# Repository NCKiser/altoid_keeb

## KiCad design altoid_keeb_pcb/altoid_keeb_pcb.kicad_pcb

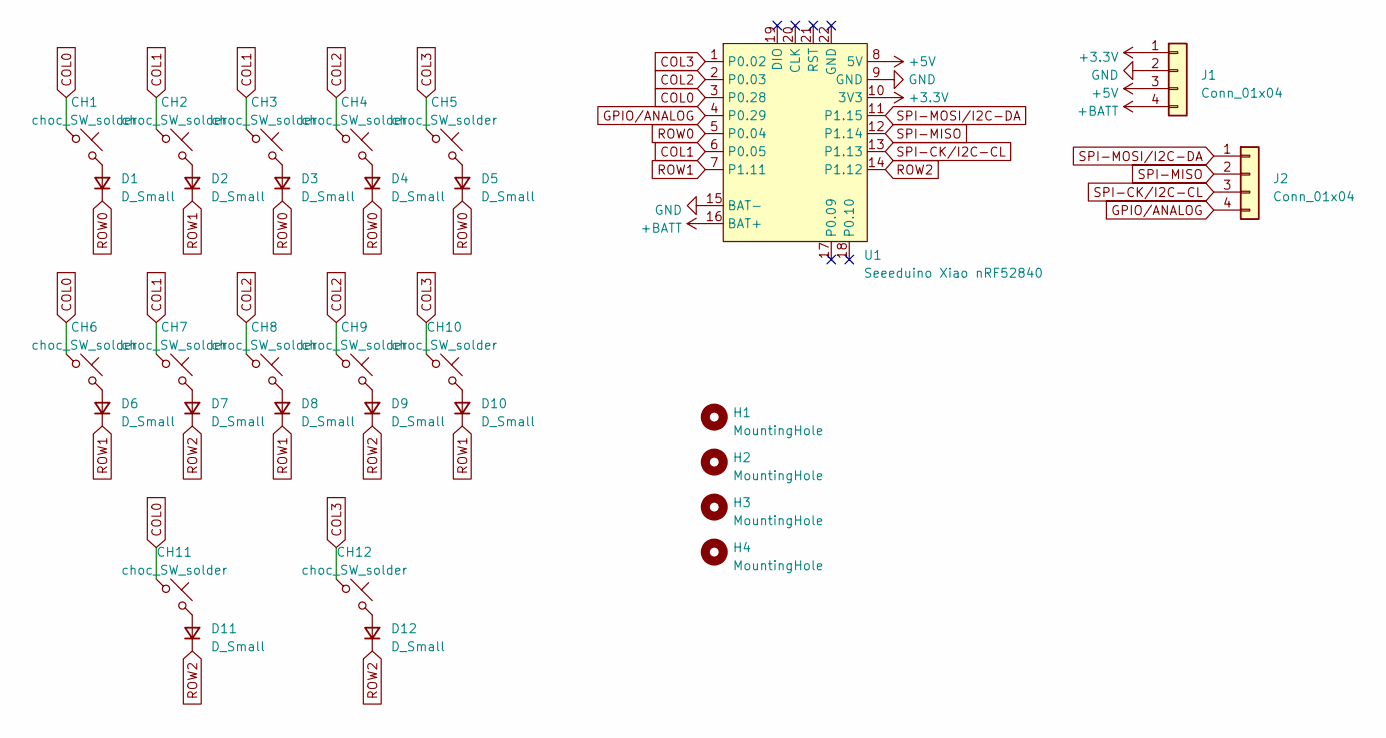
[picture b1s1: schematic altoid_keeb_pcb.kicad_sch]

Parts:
CH1, CH2, CH3, CH4, CH5, CH6, CH7, CH8, CH9, CH10, CH11, CH12: choc_SW_solder; SW_choc_v1+v2_1u
D1, D2, D3, D4, D5, D6, D7, D8, D9, D10, D11, D12: D_Small; D_DO-34_SOD68_P7.62mm_Horizontal
H1, H2, H3, H4: MountingHole; MountingHole_2.2mm_M2_Pad_Via
J1, J2: Conn_01x04; PinHeader_1x04_P2.54mm_Vertical
U1: Seeeduino Xiao nRF52840; Xiao_nRF52840_ACH

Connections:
+3.3V: J1.1, U1.10 (3V3)
+5V: J1.3, U1.8 (5V)
+BATT: J1.4, U1.16 (BAT+)
COL0: CH1.1, CH6.1, CH11.1, U1.3 (P0.28)
COL1: CH2.1, CH3.1, CH7.1, U1.6 (P0.05)
COL2: CH4.1, CH8.1, CH9.1, U1.2 (P0.03)
COL3: CH5.1, CH10.1, CH12.1, U1.1 (P0.02)
GND: J1.2, U1.9 (GND), U1.15 (BAT-)
GPIO/ANALOG: J2.4, U1.4 (P0.29)
unnamed: CH1.2, D1.2 (A)
unnamed: CH2.2, D2.2 (A)
unnamed: CH3.2, D3.2 (A)
unnamed: CH4.2, D4.2 (A)
unnamed: CH5.2, D5.2 (A)
unnamed: CH6.2, D6.2 (A)
unnamed: CH7.2, D7.2 (A)
unnamed: CH8.2, D8.2 (A)
unnamed: CH9.2, D9.2 (A)
unnamed: CH10.2, D10.2 (A)
unnamed: CH11.2, D11.2 (A)
unnamed: CH12.2, D12.2 (A)
ROW0: D1.1 (K), D3.1 (K), D4.1 (K), D5.1 (K), U1.5 (P0.04)
ROW1: D2.1 (K), D6.1 (K), D8.1 (K), D10.1 (K), U1.7 (P1.11)
ROW2: D7.1 (K), D9.1 (K), D11.1 (K), D12.1 (K), U1.14 (P1.12)
SPI-CK/I2C-CL: J2.3, U1.13 (P1.13)
SPI-MISO: J2.2, U1.12 (P1.14)
SPI-MOSI/I2C-DA: J2.1, U1.11 (P1.15)

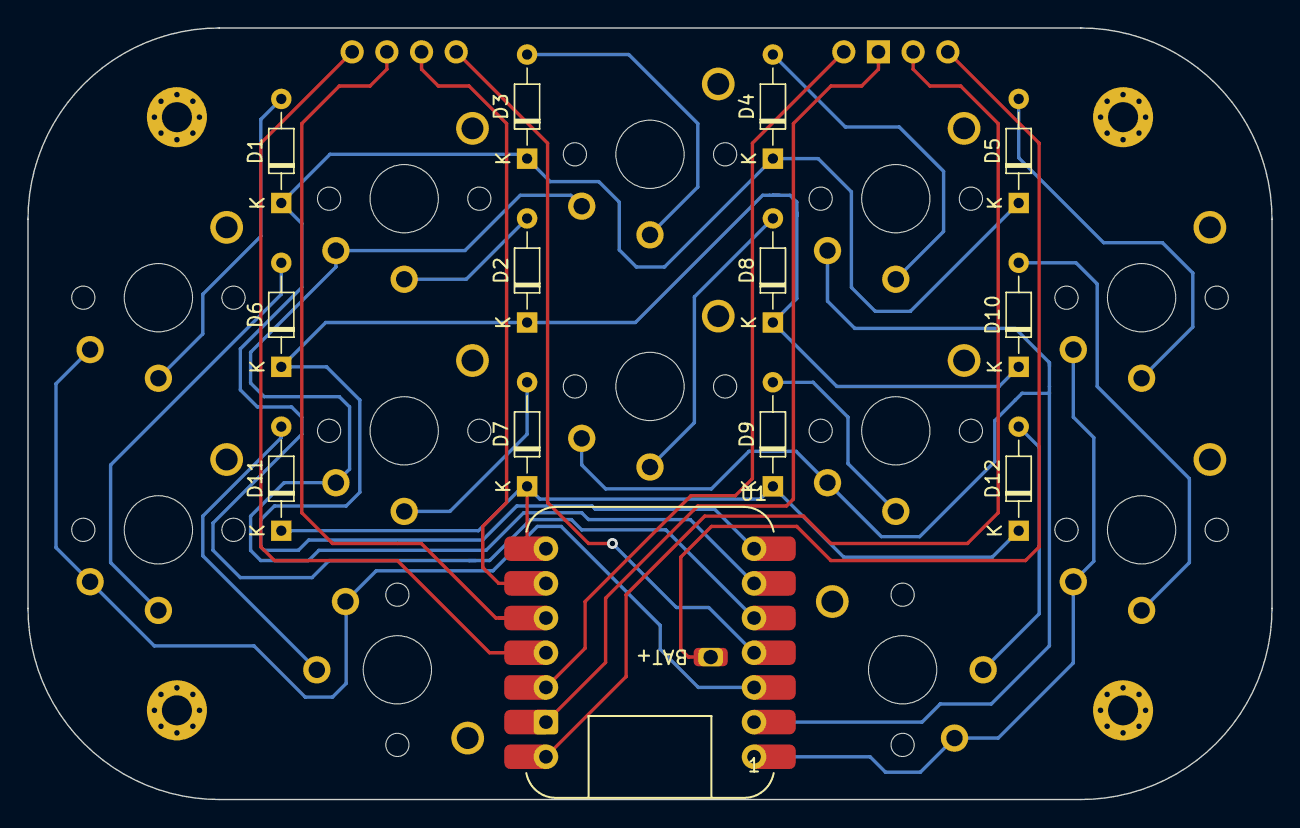
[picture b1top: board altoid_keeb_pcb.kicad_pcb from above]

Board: 2 copper layers, 91.1 x 56.5 mm, 31 parts (0 on the bottom side), 27 nets.

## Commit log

2023-11-07 init commit
2023-11-07 Routed and Placed components.
2023-11-07 add .step
